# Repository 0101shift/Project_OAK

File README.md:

# ⌚️ Project OAK (Open Art Work)

> *An approach to mimic analogue watch complications in a digital timepiece. One LED at a time.*

> ⚠️ **_Current Version: v0.1_**

> 📝 [_Version History_](Design/LLD_Design/README.md)
---

## 📁 Repository Overview

This repository contains all files related to **Project OAK**, including:

- Design files
- Datasheets
- Pin configuration sheet
- BOM (Bill of Materials)
- Source code and libraries
- Mechanical Integration files

📎 **Project OAK SCH and DSN files can be viewed on [CADLAB.io](https://cadlab.io/project/28412)**

---

## 📖 Project Overview

**Project_OAK** explores a different approach to designing digital timepieces that mimic the beauty and intricacy of **[mechanical watch complications](https://teddybaldassarre.com/blogs/watches/watch-complications?srsltid=AfmBOoqZpyDy6AT5w2ClBAenimUXbEy8DH4jYCP8Jfb1IKT3pajwjdwo)**.

While building a digitalised analogue-style watch is fairly common, recreating some of the mechanical features in a purely digital watch is both challenging and exciting.

> Although current smartwatches offer these functions via complex hardware, my goal is to **implement them using simple hardware** with minimal processing power.

- To add to its uniqueness, the **entire watch will be constructed using stacked PCBs**, which is aimed to be modular and reconfigurable based on our needs.
- The watch is designed with multiple colours and solder finishes, giving it a true electronics-nerd feel.

---

## 🎲 How it Works

> "V0.1 / V0.2" come with a simple design to set and view the time. Here’s an infographic that shows the process

---

## 🔧 Initial Prototype

📌 **[Project_OAK_MAIN_BRD_V0.1 / V0.2](Design/LLD_Design/V0.1/Project_OAK_MAIN_BRD_V0.1_RTC_Change/Project_OAK_MAIN_BRD_V0.1.pdf) is an "engineering sample".**

The primary goal of these variants is to **test all available interfaces, validate battery performance, identify design flaws, and iterate for improvements**.

Consider this board a creative playground, push its limits and explore unique feature additions for the upcoming revision.

---

## 🚀 Down the line

Though the **initial version** of Project_OAK (V0.1 / V0.2) is just a simple watch featuring a **time display** using dual-tone LEDs,

> The Future versions shall include:
> - GMT
> - Minute Repeater (ambitious!)
> - Interactive sensors (Light, IMU, Temp, Step tracking, Buzzer, etc.)
> - Higher-density LED matrix for complex visuals.
> - Position tracking using GPS, LoRa, etc. (ambitious!)
> - Exploring Low-power MCUs for long-life operation.
> - Rechargeable battery option.
> - Solar panel integration for energy harvesting.
> - ...

---

## 💎 Mechanical Integration (v0.1)

> *(These are the outputs from V0.1 variant. Design changes are expected in V0.2)*

---

## ⚙️ Getting Started

### 🔌 Programming the Board

The board can be programmed using the **Arduino IDE** via the ISP function. All the source code can be found in [ProjectOAK/codes](Codes) folder. 

#### 📝 Requirements:
- Arduino UNO/MINI/NANO/MEGA as ISP programmer
- ICSP connection to the Main Board (test points on the bottom side)

#### 💡 ICSP Programming Notes:
- ICSP pins are exposed via **Test Points** arranged in 2.4mm pitch 2x3 connector style
- Either mount **male headers** or directly solder wires for programming
- Board supports **two power options**:
  - `3V Coin Cell (default)`
  - `EXT_3V3_IN` via ICSP (requires mounting resistor R1, which is **DNI by default**)

### ⚡ Arduino IDE Settings

> - Refer to this GitHub repo on how to burn the Bootloader and how to flash code through Arduino IDE [MiniCore](https://github.com/MCUdude/MiniCore)
> - When programming the MAIN_BRD, update the ARDUINO IDE settings as shown below.

#### ❤️‍🔥 Let me know what you think of this project. I'd love to hear your thoughts!

### ✨ Happy Designing!

---

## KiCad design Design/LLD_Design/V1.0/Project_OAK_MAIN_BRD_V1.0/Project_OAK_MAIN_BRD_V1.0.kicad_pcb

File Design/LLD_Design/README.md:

# 📚 Version History

## ⛳️ V1.0 (xxx - WIP)
- Scaling down the overall thickness from 11.4 mm to 8.4 mm (except for the bottom cavity & strap PCB; the thickness of all other PCBs is reduced).
- Planning to change the coin cell from CR2032 to CR2025 and the coin cell holder to BC-2018-TR, reducing the overall battery thickness from 3.2 mm to 2.5 mm.
- Planning to move the push buttons from the top to the bottom side of the main board, since the top cavity PCB height is reduced from 1.6 mm to 1 mm.
- Planning to use a common LED color throughout the design to minimise uneven color diffusion through the PCB dials.
- Planning to increase the pull-up resistor values to reduce leakage.
- Exploring options to include an IMU (LIS2DW12) for future enhancements and upgrading the RTC to RV-3028-C7 for improved performance.
- SW optimisation to reduce current consumption for longer battery life.
- Along with the above changes, all V0.2 updates are also implemented in V1.0.

## 🔮 V0.2 (Engineering Sample2 - merging with V1.0)
- Button circuit connectivity update
- Remove the transistor configuration from the LED matrix directly. Direct connection is simple.
- Battery monitoring circuit implementation (possibly).
- Push button components to be moved towards the inner circle to avoid mechanical collision.
- Top Silk graphics to be removed from the main board.
- Main board & BOT cavity PCB dimension to be increased in the Y-direction, to match the STARP V0 board dimension
- 0E to be replaced with solder-jumpers in the LED matrix section
- DNPed MCU UART resistors
  
## 🔰 V0.1 (Engineering Sample)
- RTC changed from RX8130CE to RV-8263-C7.
- Addressed design issues with rework on the main board. Rework is documented in: [Project_OAK_MAIN_BRD_V0.1_Rework](https://github.com/0101shift/Project_OAK/blob/9e24250cb21920fe7c5c715ad4de5ba70b185401/Reworks/V0.1/README.md). 
- Cell voltage monitoring (along with LED indication) is not implemented in V0.1. Planned for V0.2
- Final testing in progress.

 <div style="background-color:#ffe6e6; padding:10px; border-radius:6px;">
⚠️ <b>Caution:</b> Other layers, except the Main Board, are reused from V0
</div>

## 🚫 V0 (Initial Design - Unreleased)
- Initial board design consists of ATmega328PB MCU, RX8130CE RTC, 36 LEDs (12H + 24M) & 2032 coin cell holder  
- The design was not released for fabrication due to a change in the RTC module.

---

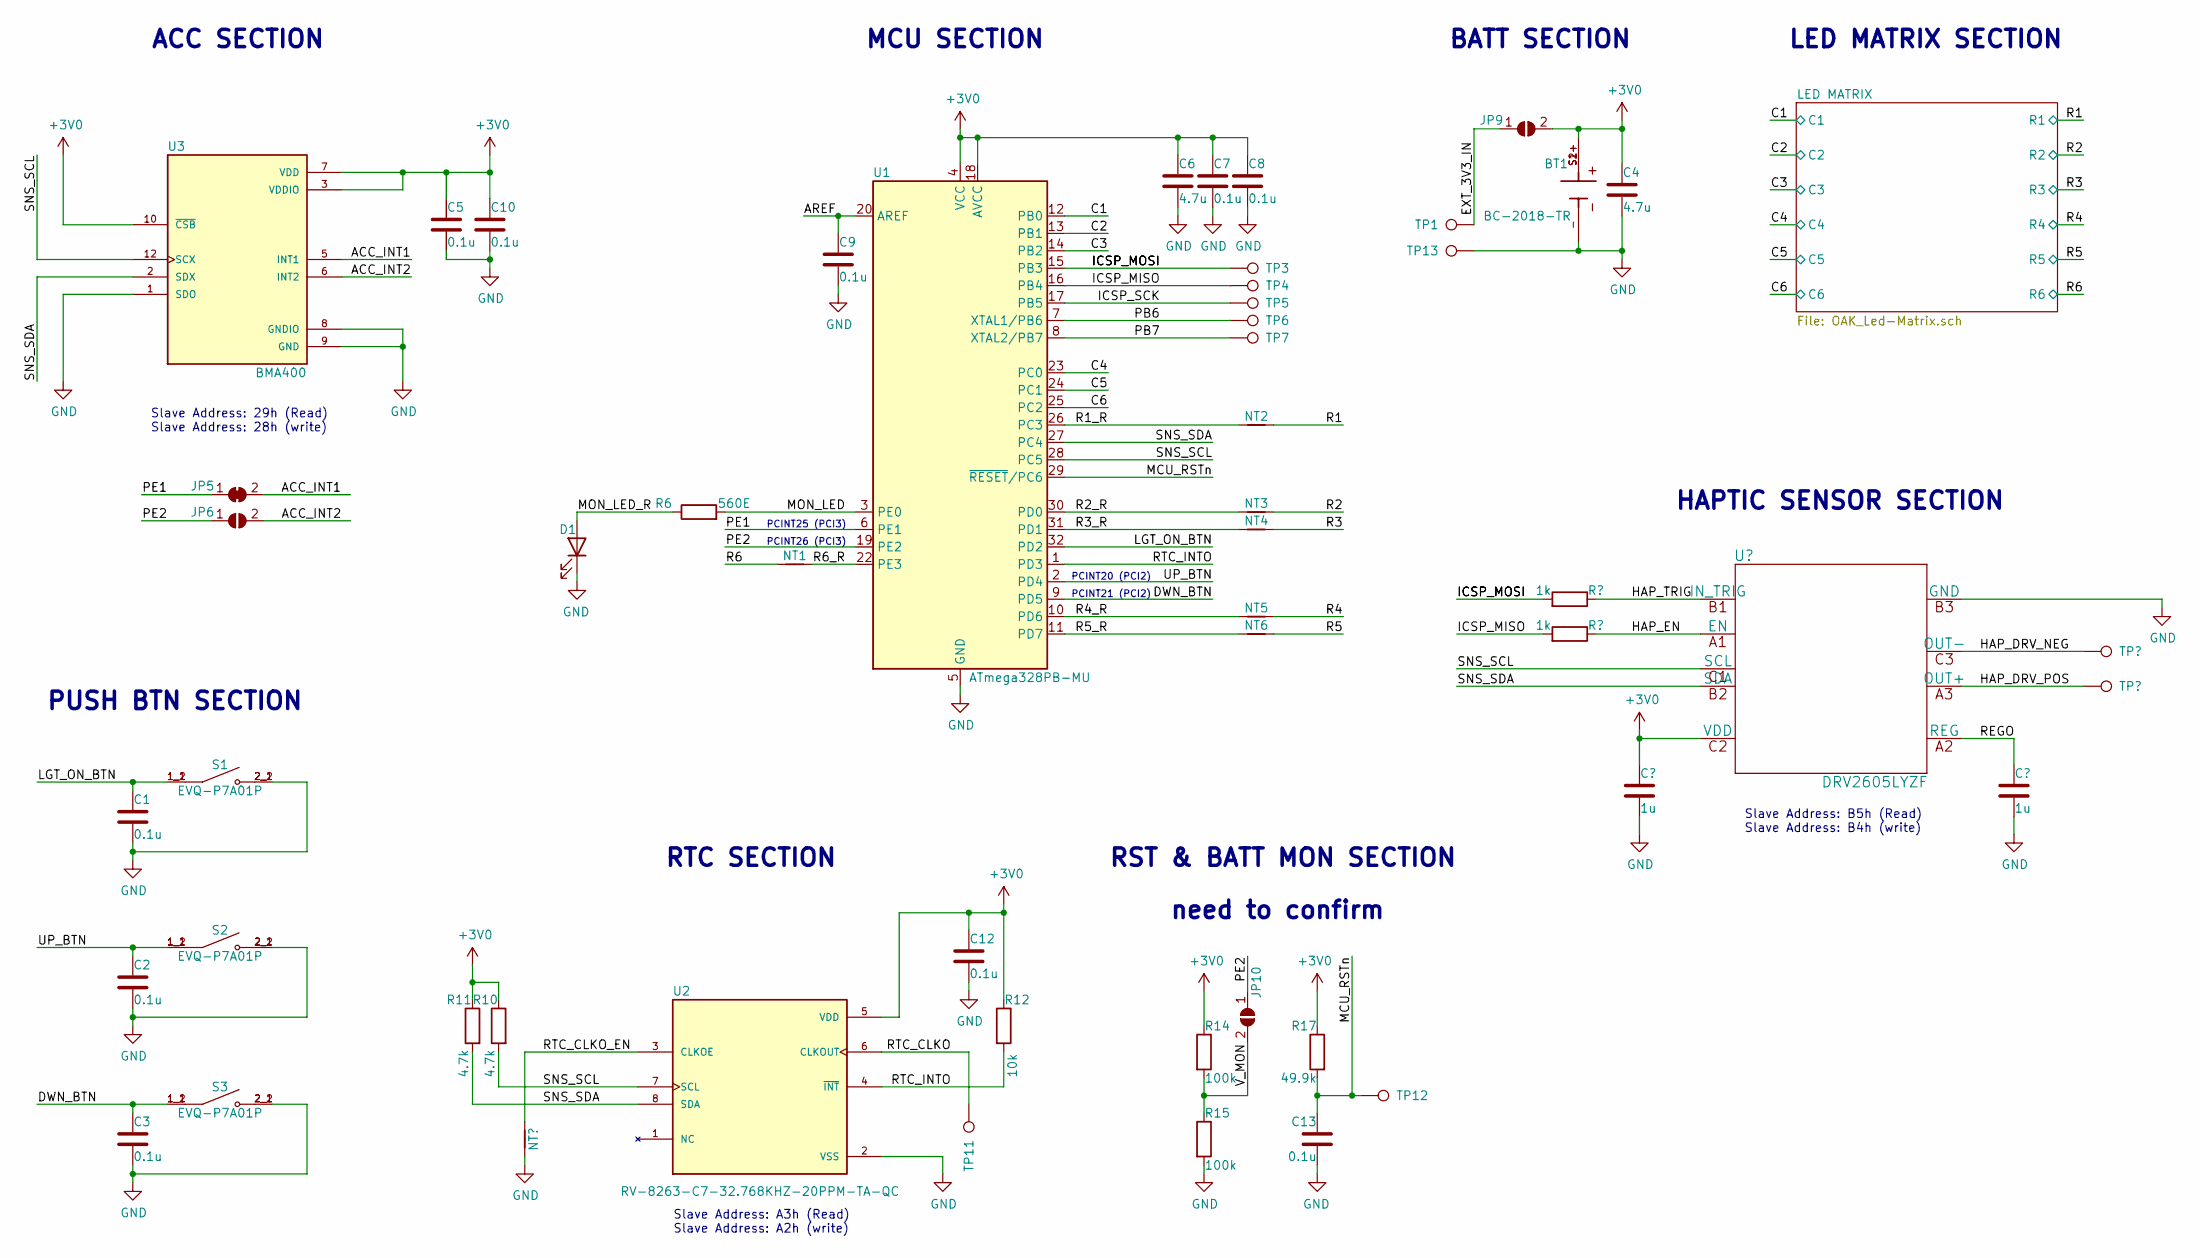
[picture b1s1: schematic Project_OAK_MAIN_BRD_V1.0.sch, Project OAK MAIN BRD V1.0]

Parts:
BT1: BC-2018-TR; BAT_BC-2018-TR; PARTREV B
C1, C2, C3, C5, C7, C8, C9, C10, C12, C13: 0.1u; C_0402_1005Metric
C4, C6: 4.7u; C_0402_1005Metric
D1: LED; LED_0402_1005Metric
JP5: SolderJumper_2_Bridged; SolderJumper-2_Bridged_Pad1.0x1.5mm_custom
JP6, JP9, JP10: SolderJumper_2_Open; SolderJumper-2_Open_Pad1.0x1.5mm_custom
NT1, NT2, NT3, NT4, NT5, NT6: Net-Tie_2; NetTie-2_SMD_Custom
R6: 560E; R_0402_1005Metric
R10, R11: 4.7k; R_0402_1005Metric
R12: 10k; R_0402_1005Metric
R14, R15: 100k; R_0402_1005Metric
R17: 49.9k; R_0402_1005Metric
S1, S2, S3: EVQ-P7A01P; SW_EVQ-P7A01P; Manufacturer_Part_Number EVQ-P7A01P; Mouser Part Number 667-EVQP7A01P
TP1, TP3, TP4, TP5, TP6, TP7, TP11, TP12, TP13: TestPoint; TestPoint_Pad_D1.0mm
U1: ATmega328PB-MU; QFN-32-1EP_5x5mm_P0.5mm_EP3.1x3.1mm
U2: RV-8263-C7-32.768KHZ-20PPM-TA-QC; PARTREV 1.0
U3: BMA400; XDCR_BMA400

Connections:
+3V0: BT1.S1+, BT1.S2+, C4.1, C5.1, C6.1, C7.1, C8.1, C10.1, C12.1, JP9.2 (B), R10.1, R11.1, R12.1, R14.1, R17.1, U1.4 (VCC), U1.18 (AVCC), U2.5 (VDD), U3.3 (VDDIO), U3.7 (VDD), U3.10 (~CSB); also elsewhere on the board
/ACC_INT1: JP5.2 (B), U3.5 (INT1)
/ACC_INT2: JP6.2 (B), U3.6 (INT2)
/AREF: C9.1, U1.20 (AREF)
/C1: U1.12 (PB0); also elsewhere on the board
/C2: U1.13 (PB1); also elsewhere on the board
/C3: U1.14 (PB2); also elsewhere on the board
/C4: U1.23 (PC0); also elsewhere on the board
/C5: U1.24 (PC1); also elsewhere on the board
/C6: U1.25 (PC2); also elsewhere on the board
/DWN_BTN: C3.1, S3.1_1, S3.1_2, U1.9 (PD5)
/EXT_3V3_IN: JP9.1 (A), TP1.1
/ICSP_MISO: TP4.1, U1.16 (PB4); also elsewhere on the board
/ICSP_MOSI: TP3.1, U1.15 (PB3); also elsewhere on the board
/ICSP_SCK: TP5.1, U1.17 (PB5)
/LGT_ON_BTN: C1.1, S1.1_1, S1.1_2, U1.32 (PD2)
/MCU_RSTn: C13.1, R17.2, TP12.1, U1.29 (~RESET~/PC6)
/MON_LED: R6.2, U1.3 (PE0)
/MON_LED_R: D1.2 (A), R6.1
/PB6: TP6.1, U1.7 (XTAL1/PB6)
/PB7: TP7.1, U1.8 (XTAL2/PB7)
/PE1: JP5.1 (A), U1.6 (PE1)
/PE2: JP6.1 (A), JP10.1 (A), U1.19 (PE2)
/R1: NT2.2; also elsewhere on the board
/R1_R: NT2.1, U1.26 (PC3)
/R2: NT3.2; also elsewhere on the board
/R2_R: NT3.1, U1.30 (PD0)
/R3: NT4.2; also elsewhere on the board
/R3_R: NT4.1, U1.31 (PD1)
/R4: NT5.2; also elsewhere on the board
/R4_R: NT5.1, U1.10 (PD6)
/R5: NT6.2; also elsewhere on the board
/R5_R: NT6.1, U1.11 (PD7)
/R6: NT1.1; also elsewhere on the board
/R6_R: NT1.2, U1.22 (PE3)
/RTC_CLKO: TP11.1, U2.6 (CLKOUT)
/RTC_CLKO_EN: U2.3 (CLKOE); also elsewhere on the board
/RTC_INTO: R12.2, U1.1 (PD3), U2.4 (~INT)
/SNS_SCL: R10.2, U1.28 (PC5), U2.7 (SCL), U3.12 (SCX); also elsewhere on the board
/SNS_SDA: R11.2, U1.27 (PC4), U2.8 (SDA), U3.2 (SDX); also elsewhere on the board
/UP_BTN: C2.1, S2.1_1, S2.1_2, U1.2 (PD4)
/V_MON: JP10.2 (B), R14.2, R15.1
GND: BT1.-, C1.2, C2.2, C3.2, C4.2, C5.2, C6.2, C7.2, C8.2, C9.2, C10.2, C12.2, C13.2, D1.1 (K), R15.2, S1.2_1, S1.2_2, S2.2_1, S2.2_2, S3.2_1, S3.2_2, TP13.1, U1.5 (GND), U1.21 (GND), U1.33 (GND), U2.2 (VSS), U3.1 (SDO), U3.8 (GNDIO), U3.9 (GND); also elsewhere on the board

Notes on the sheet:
PUSH BTN SECTION
BATT SECTION
MCU SECTION
Slave Address: A3h (Read) Slave Address: A2h (write)
LED MATRIX SECTION
ACC SECTION
need to confirm
RST & BATT MON SECTION
Slave Address: 29h (Read) Slave Address: 28h (write)
RTC SECTION
PCINT25 (PCI3)
PCINT26 (PCI3)
PCINT20 (PCI2)
PCINT21 (PCI2)
HAPTIC SENSOR SECTION
Slave Address: B5h (Read) Slave Address: B4h (write)

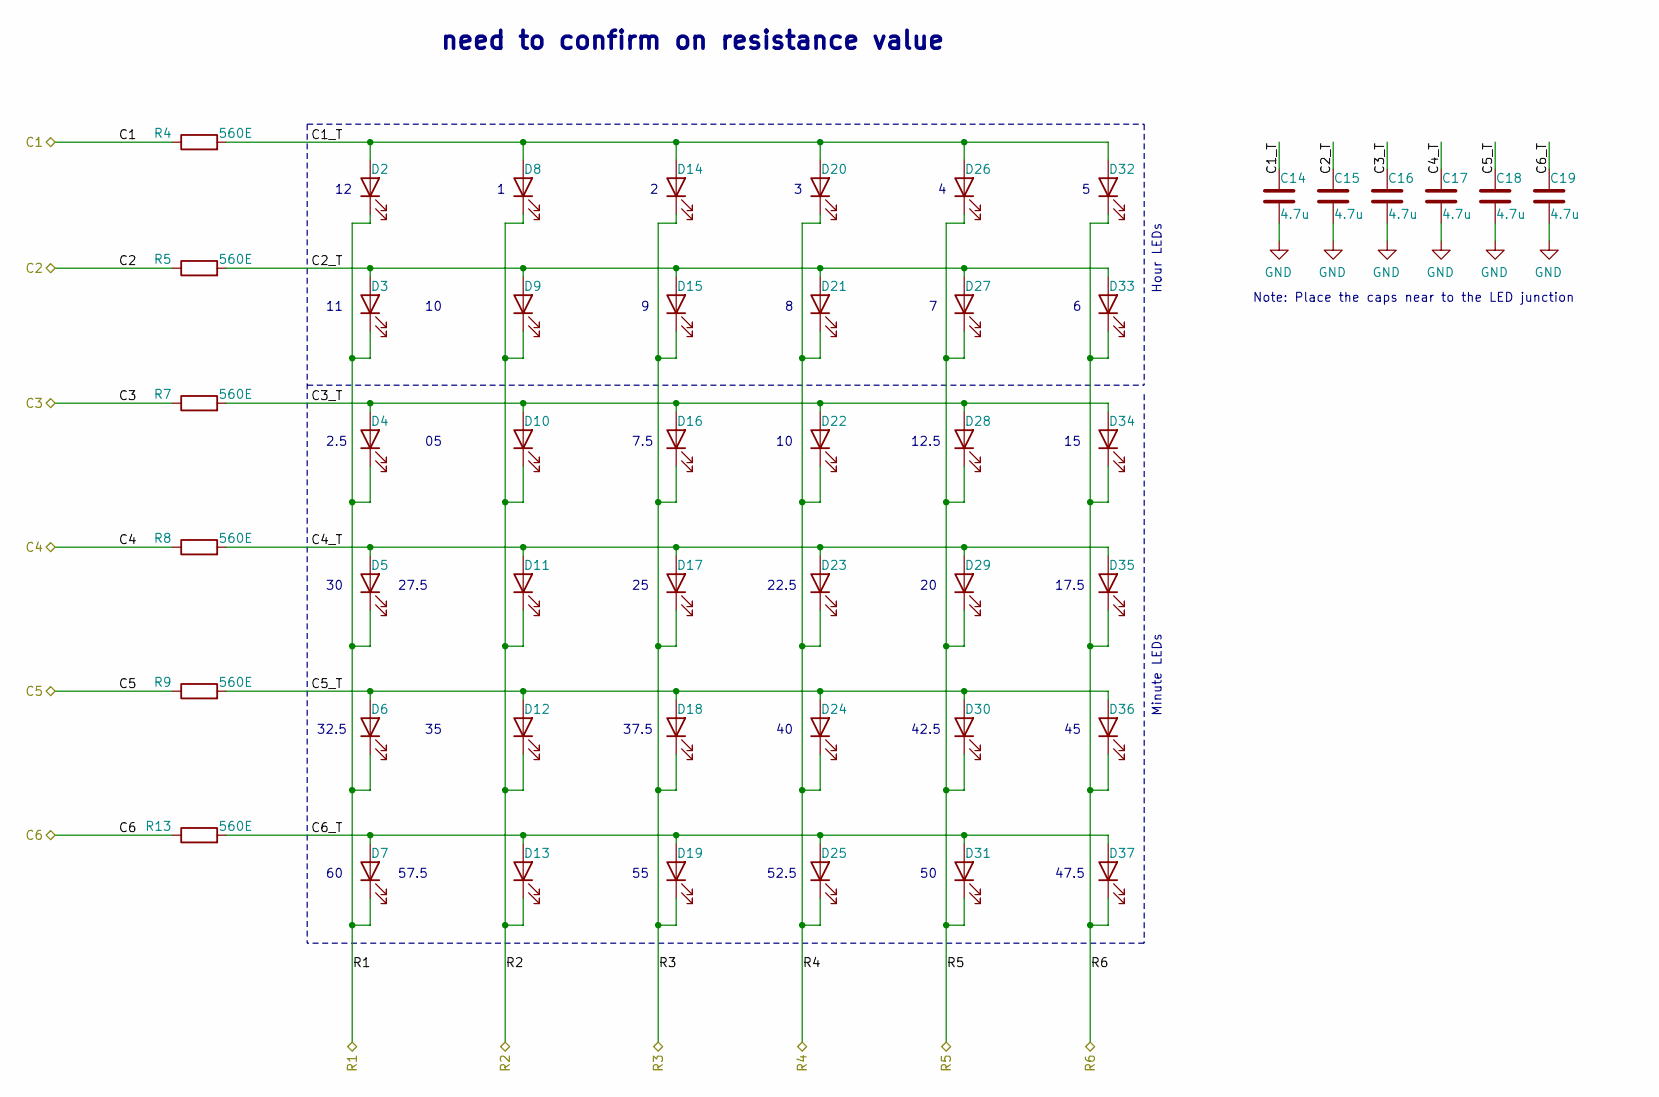
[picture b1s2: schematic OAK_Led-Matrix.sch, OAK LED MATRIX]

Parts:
C14, C15, C16, C17, C18, C19: 4.7u; C_0402_1005Metric
D2, D3, D4, D5, D6, D7, D8, D9, D10, D11, D12, D13, D14, D15, D16, D17, D18, D19, D20, D21, D22, D23, D24, D25, D26, D27, D28, D29, D30, D31, D32, D33, D34, D35, D36, D37: LED; LED_0402_1005Metric
R4, R5, R7, R8, R9, R13: 560E; R_0402_1005Metric

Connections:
/C1: R4.1; also elsewhere on the board
/C2: R5.1; also elsewhere on the board
/C3: R7.1; also elsewhere on the board
/C4: R8.1; also elsewhere on the board
/C5: R9.1; also elsewhere on the board
/C6: R13.1; also elsewhere on the board
/LED MATRIX/C1_T: C14.1, D2.2 (A), D8.2 (A), D14.2 (A), D20.2 (A), D26.2 (A), D32.2 (A), R4.2
/LED MATRIX/C2_T: C15.1, D3.2 (A), D9.2 (A), D15.2 (A), D21.2 (A), D27.2 (A), D33.2 (A), R5.2
/LED MATRIX/C3_T: C16.1, D4.2 (A), D10.2 (A), D16.2 (A), D22.2 (A), D28.2 (A), D34.2 (A), R7.2
/LED MATRIX/C4_T: C17.1, D5.2 (A), D11.2 (A), D17.2 (A), D23.2 (A), D29.2 (A), D35.2 (A), R8.2
/LED MATRIX/C5_T: C18.1, D6.2 (A), D12.2 (A), D18.2 (A), D24.2 (A), D30.2 (A), D36.2 (A), R9.2
/LED MATRIX/C6_T: C19.1, D7.2 (A), D13.2 (A), D19.2 (A), D25.2 (A), D31.2 (A), D37.2 (A), R13.2
/R1: D2.1 (K), D3.1 (K), D4.1 (K), D5.1 (K), D6.1 (K), D7.1 (K); also elsewhere on the board
/R2: D8.1 (K), D9.1 (K), D10.1 (K), D11.1 (K), D12.1 (K), D13.1 (K); also elsewhere on the board
/R3: D14.1 (K), D15.1 (K), D16.1 (K), D17.1 (K), D18.1 (K), D19.1 (K); also elsewhere on the board
/R4: D20.1 (K), D21.1 (K), D22.1 (K), D23.1 (K), D24.1 (K), D25.1 (K); also elsewhere on the board
/R5: D26.1 (K), D27.1 (K), D28.1 (K), D29.1 (K), D30.1 (K), D31.1 (K); also elsewhere on the board
/R6: D32.1 (K), D33.1 (K), D34.1 (K), D35.1 (K), D36.1 (K), D37.1 (K); also elsewhere on the board
GND: C14.2, C15.2, C16.2, C17.2, C18.2, C19.2; also elsewhere on the board

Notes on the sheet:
Hour LEDs
Minute LEDs
2.5
7.5
12.5
17.5
22.5
27.5
32.5
37.5
42.5
47.5
52.5
57.5
need to confirm on resistance value
Note: Place the caps near to the LED junction

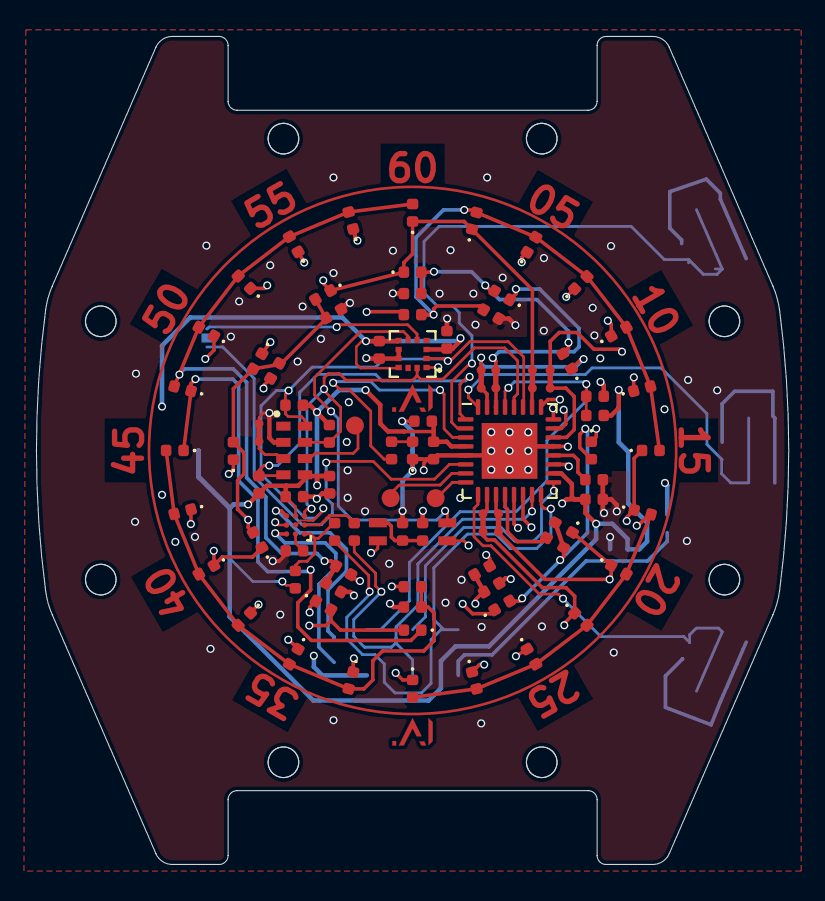
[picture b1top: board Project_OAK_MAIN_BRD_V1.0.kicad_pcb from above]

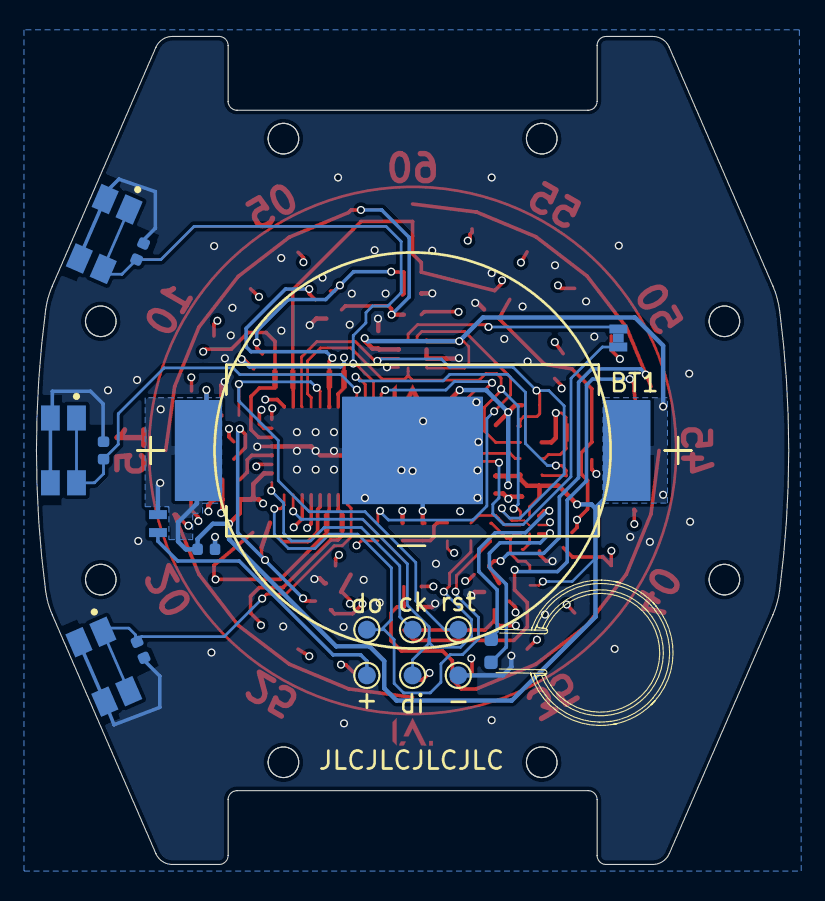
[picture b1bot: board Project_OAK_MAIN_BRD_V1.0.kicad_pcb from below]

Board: 4 copper layers, 41.8 x 46.0 mm, 104 parts (19 on the bottom side), 54 nets.

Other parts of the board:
BT1#2: BC-2018-TR; BAT_BC-2018-TR
C11, C20: 1u; C_0402_1005Metric
NT7: Net-Tie_2; NetTie-2_SMD_Custom
R1, R2: 1k; R_0402_1005Metric
R3: 100k; R_0402_1005Metric
TP2, TP8: TestPoint; TestPoint_Pad_D1.0mm
U4: DRV2605LYZF; DRV2605LYZFR

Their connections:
+3V0: BT1#2.S1+, BT1#2.S2+, C11.1, R3.1, U4.C2; also elsewhere on the board
/HAP_DRV_NEG: TP2.1, U4.C3
/HAP_DRV_POS: TP8.1, U4.A3
/HAP_EN: R2.1, R3.2, U4.A1
/HAP_TRIG: R1.1, U4.B1
/ICSP_MISO: R2.2; also elsewhere on the board
/ICSP_MOSI: R1.2; also elsewhere on the board
/REGO: C20.1, U4.A2
/RTC_CLKO_EN: NT7.1; also elsewhere on the board
/SNS_SCL: U4.C1; also elsewhere on the board
/SNS_SDA: U4.B2; also elsewhere on the board
GND: BT1#2.-, C11.2, C20.2, NT7.2, U4.B3; also elsewhere on the board

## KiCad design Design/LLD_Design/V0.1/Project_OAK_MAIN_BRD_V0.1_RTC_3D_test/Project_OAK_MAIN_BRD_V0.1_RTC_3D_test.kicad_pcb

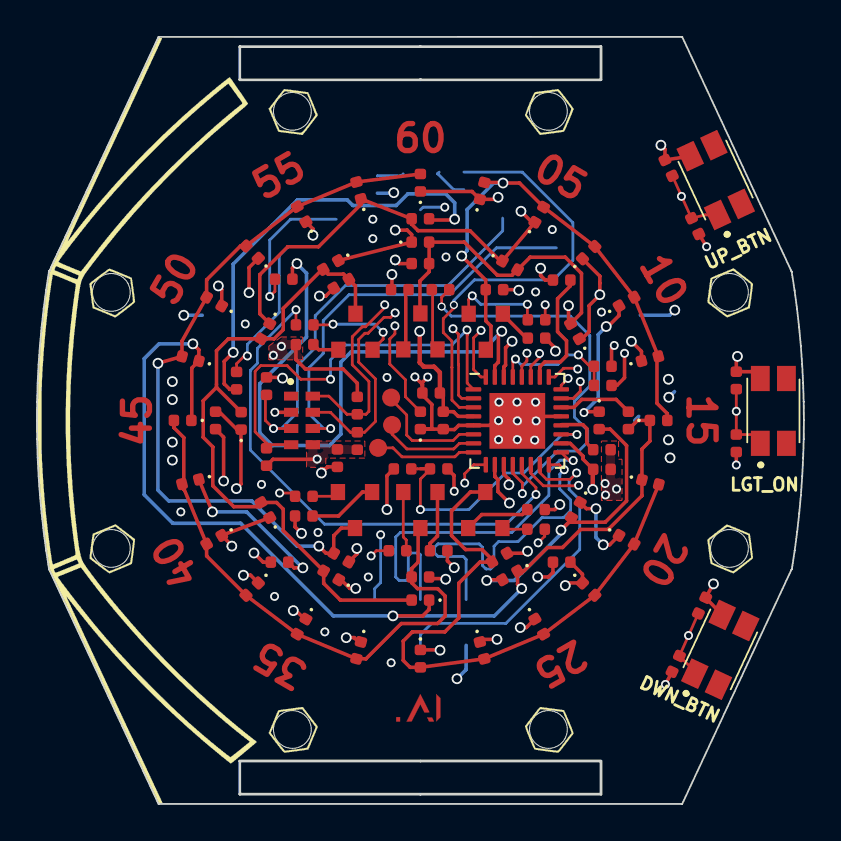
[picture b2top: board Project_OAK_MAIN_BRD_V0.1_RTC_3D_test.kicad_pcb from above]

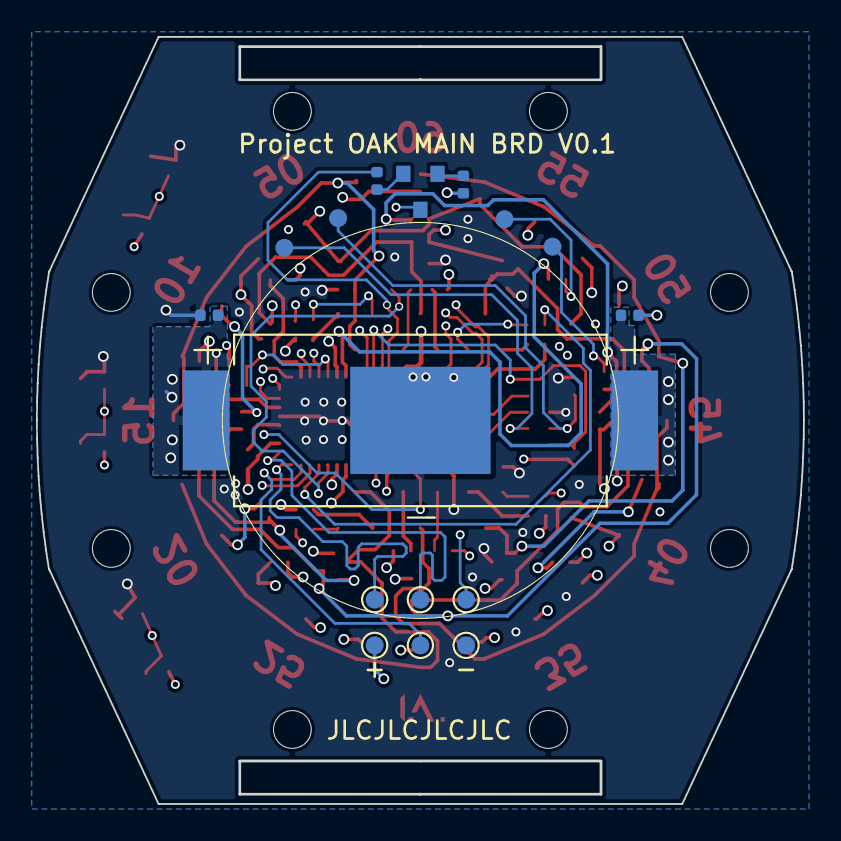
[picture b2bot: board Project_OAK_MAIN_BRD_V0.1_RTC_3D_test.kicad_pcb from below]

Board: 6 copper layers, 42.6 x 42.6 mm, 112 parts (16 on the bottom side), 62 nets.

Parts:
BT1: BC-2003; BAT_BC-2003
C1, C2, C3, C7, C8, C9, C12, C13: 0.1u; C_0402_1005Metric
C4, C6, C14, C15, C16, C17, C18, C19: 4.7u; C_0402_1005Metric
D1, D2, D3, D4, D5, D6, D7, D8, D9, D10, D11, D12, D13, D14, D15, D16, D17, D18, D19, D20, D21, D22, D23, D24, D25, D26, D27, D28, D29, D30, D31, D32, D33, D34, D35, D36, D37: LED; LED_0402_1005Metric
Q1, Q2, Q3, Q4, Q5, Q6, Q7: BC547; SOT-23
R1, R28, R29, R30, R31, R32, R33: 0E; R_0402_1005Metric
R2, R3, R4, R7, R14, R15, R17: 10k; R_0402_1005Metric
R5: 1K; R_0402_1005Metric
R6, R13, R18, R19, R22, R23, R26: 10K; R_0402_1005Metric
R8, R9: 1k; R_0402_1005Metric
R10, R11, R12: 4.7K; R_0402_1005Metric
R16, R20, R21, R24, R25, R27: 120E; R_0402_1005Metric
S1, S2, S3: EVQ-P7A01P; EVQP7J01P
TP1, TP2, TP3, TP4, TP5, TP6, TP7, TP8, TP9, TP10, TP11, TP12, TP13: TestPoint; TestPoint_Pad_D1.0mm
U1: ATmega328PB-MU; QFN-32-1EP_5x5mm_P0.5mm_EP3.1x3.1mm
U2: RV-8263-C7-32.768KHZ-20PPM-TA-QC

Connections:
+3V0: BT1.S1+, BT1.S2+, C4.1, C6.1, C7.1, C8.1, C12.1, R1.2, R2.1, R3.1, R4.1, R5.2, R10.1, R11.1, R12.1, R14.1, R16.2, R17.1, R20.2, R21.2, R24.2, R25.2, R27.2, U1.4, U1.18, U2.5
/+3V0_MON_LED: R6.2, U1.3
/+3V0_VOL_MON: R14.2, R15.1, U1.19
/AREF: C9.1, U1.20
/C1: R26.1, U1.12
/C1_T: C14.1, D2.2, D8.2, D14.2, D20.2, D26.2, D32.2, Q7.3
/C2: R23.1, U1.13
/C2_T: C15.1, D3.2, D9.2, D15.2, D21.2, D27.2, D33.2, Q6.3
/C3: R22.1, U1.14
/C3_T: C16.1, D4.2, D10.2, D16.2, D22.2, D28.2, D34.2, Q5.3
/C4: R19.1, U1.23
/C4_T: C17.1, D5.2, D11.2, D17.2, D23.2, D29.2, D35.2, Q4.3
/C5: R18.1, U1.24
/C5_T: C18.1, D6.2, D12.2, D18.2, D24.2, D30.2, D36.2, Q3.3
/C6: R13.1, U1.25
/C6_T: C19.1, D7.2, D13.2, D19.2, D25.2, D31.2, D37.2, Q2.3
/DBG_RX: R8.2, TP9.1
/DBG_TX: R9.2, TP10.1
/DWN_BTN: C3.1, R4.2, S3.1, U1.9
/EXT_3V3_IN: R1.1, TP1.1
/ICSP_MISO: TP4.1, U1.16
/ICSP_MOSI: TP3.1, U1.15
/ICSP_SCK: TP5.1, U1.17
/LGT_ON_BTN: C1.1, R2.2, S1.1, U1.32
/MCU_RSTn: C13.1, R17.2, TP12.1, U1.29
/PB6: TP6.1, U1.7
/PB7: TP7.1, U1.8
/PE1: TP2.1, U1.6
/R1: D2.1, D3.1, D4.1, D5.1, D6.1, D7.1, R29.2
/R1_R: R29.1, U1.26
/R2: D8.1, D9.1, D10.1, D11.1, D12.1, D13.1, R32.2
/R2_R: R8.1, R32.1, U1.30
/R3: D14.1, D15.1, D16.1, D17.1, D18.1, D19.1, R33.2
/R3_R: R9.1, R33.1, U1.31
/R4: D20.1, D21.1, D22.1, D23.1, D24.1, D25.1, R30.2
/R4_R: R30.1, U1.10
/R5: D26.1, D27.1, D28.1, D29.1, D30.1, D31.1, R31.2
/R5_R: R31.1, U1.11
/R6: D32.1, D33.1, D34.1, D35.1, D36.1, D37.1, R28.1
/R6_R: R28.2, U1.22
/RTC_CLKO: TP11.1, U2.6
/RTC_CLKO_EN: R7.1, TP8.1, U2.3
/RTC_INTO: R12.2, U1.1, U2.4
/RTC_SCL: R10.2, U1.28, U2.7
/RTC_SDA: R11.2, U1.27, U2.8
/UP_BTN: C2.1, R3.2, S2.1, U1.2
GND: BT1.-, C1.2, C2.2, C3.2, C4.2, C6.2, C7.2, C8.2, C9.2, C12.2, C13.2, C14.2, C15.2, C16.2, C17.2, C18.2, C19.2, D1.1, R7.2, R15.2, S1.2, S2.2, S3.2, TP13.1, U1.5, U1.21, U1.33, U2.2
unnamed: D1.2, Q1.3
unnamed: Q1.1, R5.1
unnamed: Q1.2, R6.1
unnamed: Q2.1, R16.1
unnamed: Q2.2, R13.2
unnamed: Q3.1, R20.1
unnamed: Q3.2, R18.2
unnamed: Q4.1, R21.1
unnamed: Q4.2, R19.2
unnamed: Q5.1, R24.1
unnamed: Q5.2, R22.2
unnamed: Q6.1, R25.1
unnamed: Q6.2, R23.2
unnamed: Q7.1, R27.1
unnamed: Q7.2, R26.2

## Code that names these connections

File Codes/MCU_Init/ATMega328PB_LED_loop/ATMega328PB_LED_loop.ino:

/*********************************************************************
  Simple AVR sketch to blink Hour & Minute LEDs in a random loop
  For WATCH LEDs mapping, check the Project_OAK_MCU_Pinouts.xlsx excel
**********************************************************************/

#include <avr/io.h>
#include <util/delay.h>

typedef struct {
  volatile uint8_t *port;
  uint8_t pin;
} led;

led leds[] = {
  {&PORTB, PB0}, {&PORTB, PB1}, {&PORTB, PB2},
  {&PORTC, PC0}, {&PORTC, PC1}, {&PORTC, PC2},
  {&PORTC, PC3}, {&PORTD, PD0}, {&PORTD, PD1},
  {&PORTD, PD6}, {&PORTD, PD7}, {&PORTE, PE3}
};

uint8_t ledcount = sizeof(leds) / sizeof(leds[0]);

void setup()
{
  for (uint8_t i = 0; i < ledcount; i++)
  {
    if (leds[i].port == &PORTB)
    {
      DDRB |= (1 << leds[i].pin);
    }
    else if (leds[i].port == &PORTC)
    {
      DDRC |= (1 << leds[i].pin);
    }
    else if (leds[i].port == &PORTD)
    {
      DDRD |= (1 << leds[i].pin);
    }
    else if (leds[i].port == &PORTE)
    {
      DDRE |= (1 << leds[i].pin);
    }
  }
}

int main (void)
{
  setup();

  while (1) {
    ledblink(100);
  }
  return 0;
}

void ledblink (uint16_t delaytime)
{
  for (uint8_t i = 0; i < ledcount / 2; i++)
  {
    *(leds[i].port) ^= (1 << leds[i].pin);
    _delay_ms(delaytime);
    for (uint8_t j = ledcount / 2; j < ledcount; j++)
    {
      *(leds[j].port) ^= (1 << leds[j].pin);
      _delay_ms(delaytime);
    }
  }
}

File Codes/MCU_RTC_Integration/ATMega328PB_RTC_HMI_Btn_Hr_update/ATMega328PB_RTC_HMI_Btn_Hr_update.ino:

/**********************************************************************************************************
  Simple AVR sketch demonstrate the interface of RTC sensor RV-8263-C7 with ATMega328PB. This code is to
  execute Hour, Minute & MI functions of the RTC sensor and outputs the data using on-board LEDs (visulization).
  Post power on, MCU goes to sleep and wakes up on interrupt generated either by the RTC sensor (every minute)
  or with button press (PWR BTN). based on the button press duration, specific set of actions are performed.
  If button press short (50ms), the device outputs RTC sensor data by lighting up the LEDs (Time Indication)
  and goes back to sleep. If button press long (1000ms), the device wakes up from pwr-down mode and stays
  in active state by blinking all the LEDs onboard (100ms). This allows user to update Time by pressing
  UP & DWN button to adjust Hour time respectively. Once updated time, the device is put back to sleep 
  by short pressing the PWR button.

  Sketch uses "OakLedMatrix" lib which takes care of mapping LED pins to their respective Hr/Min positions
  Sketch uses "RV-8263-C7" lib which takes care of interface between MCU and RV-8263-C7 RTC sensor

  Here are the list of registers that are modified / accessed in this program

  |Register|         |Function|      |Bit7|  |Bit6|  |Bit5|  |Bit4|  |Bit3|  |Bit2|  |Bit1|  |Bit0|
  |                                                                                               |
  |  01h   |         |Control2|      |AIE |  | AF |  | MI |  |HMI |  | TF |  | FD|   | FD |  | FD |
  |  04h   |         |Seconds|       | OS |  | 40 |  | 20 |  | 10 |  | 8  |  | 4 |   | 2 |   | 1  |
  |  05h   |         |minutes|       | X  |  | 40 |  | 20 |  | 10 |  | 8  |  | 4 |   | 2 |   | 1  |
  |  06h   |          |Hours|        | X  |  | X  |  |AMPM|  | 10 |  | 8  |  | 4 |   | 2 |   | 1  |
  |  07h   |          |Date|         | X  |  | X  |  | 20 |  | 10 |  | 8  |  | 4 |   | 2 |   | 1  |
  |  08h   |         |Weekday|       | X  |  | X  |  | X  |  | X  |  | X  |  | 4 |   | 2 |   | 1  |
  |  09h   |          |Month|        | X  |  | X  |  | X  |  | 10 |  | 8  |  | 4 |   | 2 |   | 1  |
  |  0Ah   |          |Year|         | 80 |  | 40 |  | 20 |  | 10 |  | 8  |  | 4 |   | 2 |   | 1  |
  |  11h   |       |Timer Mode|      | X  |  | X  |  | X  |  | TD |  | TD |  |TE |   |TIE|  |TI_TP|
**********************************************************************************************************/

#include <avr/io.h>
#include <avr/sleep.h>
#include <util/delay.h>
#include <RV-8263-C7.h>
#include <OakLedMatrix.h>
#include <math.h>

#define HMI_INTERRUPT_PIN PD3   // RTC interrupt (INT1)
#define PWR_BUTTON_PIN PD2   // Push button interrupt (INT0)
#define UP_BUTTON_PIN PD4       // Button to increase value
#define DWN_BUTTON_PIN PD5      // Button to decrease value
#define SHORT_PRESS_DURATION 50   // Duration in milliseconds
#define LONG_PRESS_DURATION 1000  // Duration in milliseconds

volatile bool wakeUpFlag = false;      // Interrupt flag to indicate wake-up event
volatile uint16_t pressDuration = 0;   // Stores button press timestamp
volatile bool buttonPressed = false;   // Flag for button press event
volatile uint8_t stayAwake = false;    // Flag to keep MCU awake
volatile bool inUpdateMode = false; // Flag to track update mode

void setup() {
  initMatrix();
  initRTC();
  _delay_ms(1000);

  // Configure RTC for Half-Minute Interrupt (HMI)
  writeRegister(0x01, 0b00100000); // Set periodic interrupt to Minute
  writeRegister(0x11, 0b00011001); // Enable periodic interrupt

  // Configure PD3 (INT1) for RTC interrupt (falling edge)
  DDRD &= ~(1 << HMI_INTERRUPT_PIN); // Set PD3 as input
  PORTD |= (1 << HMI_INTERRUPT_PIN); // Enable pull-up resistor on PD3
  EICRA |= (1 << ISC11); // Falling edge triggers INT1
  EICRA &= ~(1 << ISC10);
  EIMSK |= (1 << INT1);  // Enable INT1 interrupt

  // Configure PD2 (INT0) for push-button wake-up (falling edge)
  DDRD &= ~(1 << PWR_BUTTON_PIN); // Set PD2 as input
  PORTD |= (1 << PWR_BUTTON_PIN); // Enable pull-up resistor on PD3
  EICRA |= (1 << ISC01);
  EICRA &= ~(1 << ISC00);
  EIMSK |= (1 << INT0);  // Enable INT0 interrupt

  // Configure navigation buttons (PD4, PD5) as inputs with pull-ups
  DDRD &= ~((1 << UP_BUTTON_PIN) | (1 << DWN_BUTTON_PIN));
  PORTD |= (1 << UP_BUTTON_PIN) | (1 << DWN_BUTTON_PIN);

  sei(); // Enable global interrupts
}

// Interrupt Service Routine (ISR) for RTC wake-up on PD3 (INT1)
ISR(INT1_vect) {
  wakeUpFlag = true;
}

// Interrupt Service Routine (ISR) for push-button wake-up on PD2 (INT0)
ISR(INT0_vect) {
  buttonPressed = true;  // Flag to handle the button press in the main loop
}

void loop() {
  if (buttonPressed) {
    _delay_ms(50);  // Basic debounce delay
    buttonPressed = false;

    // Measure press duration
    pressDuration = 0;
    while (!(PIND & (1 << PWR_BUTTON_PIN))) {
      _delay_ms(10);  // Increment duration in 10ms steps
      pressDuration += 10;
      if (pressDuration >= LONG_PRESS_DURATION) {
        break;  // Stop counting if long press is detected
      }
    }

    if (pressDuration >= LONG_PRESS_DURATION) {
      stayAwake = true;  // Set stayAwake, preventing sleep
      functionLongPress();
      enterUpdateMode();
    } else if (pressDuration >= SHORT_PRESS_DURATION) {
      stayAwake = false;  // Allow sleep
      functionShortPress();
    }
  }

  if (wakeUpFlag) {
    wakeUpFlag = false;
    displayTime();
  }

  if (!stayAwake && !inUpdateMode) {
    enterSleepMode();
  }
}

// Function to enter power-down sleep mode
void enterSleepMode() {
  set_sleep_mode(SLEEP_MODE_PWR_DOWN); // Power-down mode
  sleep_enable(); // Enable sleep mode
  sleep_cpu(); // Enter sleep mode (wait for interrupt)
  sleep_disable(); // Disable sleep after waking up
}

// Function to get RTC time and display it using LED matrix
void displayTime() {
  uint8_t hours, minutes, seconds, date, day, month, year;
  const char period[3];

  getTime(hours, minutes, seconds, date, day, month, year, period);

  // Convert minutes to corresponding LED index (2.5 min per LED)
  uint8_t minuteMap = round(minutes / 2.5);

  // Show hour and minute time for 1 second
  uint16_t displayDuration = 500 / 10;  // 100ms per toggle for 0.5 second

  for (uint16_t i = 0; i < displayDuration; i++) {
    LedClockHourTime(hours);
    _delay_ms(5);
    LedClockMinuteTime(minuteMap);
    _delay_ms(5);
  }

  deactivateLedMatrix(); // Turn off LEDs
}

// === Short Press Function ===
void functionShortPress() {
  displayTime();
}

// === Long Press Function ===
void functionLongPress() {
  activateLedMatrixAll();
  _delay_ms(100);
  deactivateLedMatrix();
  _delay_ms(100);
}

// === LED Navigation Mode for Setting Hour ===
void enterUpdateMode() {
  inUpdateMode = true;
  uint8_t newHour = 12; // Default hour selection
  uint8_t up_button_state, dwn_button_state, pwr_button_state;
  uint8_t last_button_state = 0;

  while (inUpdateMode) {
    // Read button states
    up_button_state = PIND & (1 << UP_BUTTON_PIN);
    dwn_button_state = PIND & (1 << DWN_BUTTON_PIN);
    pwr_button_state = PIND & (1 << PWR_BUTTON_PIN);

    // If any button was pressed
    if ((up_button_state == 0 && last_button_state != 0) ||
        (dwn_button_state == 0 && last_button_state != 0) ||
        (pwr_button_state == 0 && last_button_state != 0)) {

      _delay_ms(50); // Debounce delay

      // Increase hour
      if ((PIND & (1 << UP_BUTTON_PIN)) == 0) {
        newHour = (newHour == 12) ? 1 : newHour + 1;
      }

      // Decrease hour
      if ((PIND & (1 << DWN_BUTTON_PIN)) == 0) {
        newHour = (newHour == 1) ? 12 : newHour - 1;
      }

      // Confirm and update RTC
      if ((PIND & (1 << PWR_BUTTON_PIN)) == 0) {
        updateRTC(newHour);
        inUpdateMode = false;
        return;
      }
    }

    // Display hour LED navigation
    LedClockHourTime(newHour);
    _delay_ms(100); // Small delay to improve responsiveness

    // Store last button state
    last_button_state = up_button_state | dwn_button_state | pwr_button_state;
  }
}

// === Update RTC with New Hour ===
void updateRTC(uint8_t newHour) {
  uint8_t nowHour, nowMinutes, nowSeconds, nowDate, nowDay, nowMonth, nowYear;
  const char nowPeriod[3];

  getTime(nowHour, nowMinutes, nowSeconds, nowDate, nowDay, nowMonth, nowYear, nowPeriod);
  updateTime(newHour, nowMinutes, nowSeconds, nowDate, nowDay, nowMonth, nowYear, nowPeriod);
}

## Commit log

2024-09-01 Initial Commit
    These are the basic codes that is used to perform basic bring-up on Project_OAK_MAIN_BRD_V0.1 board.
2024-09-01 Project Initial Commit
2024-09-01 Backlink to CADLAB.io has been added.
2024-09-04 Added RTC sensor Initialization codes
2024-09-05 Added multiple INT wake function for MCU with RTC timestamp
2024-09-11 Updated README.md with Steps to program the Main Board
2024-09-11 Added datasheet and gitignore list
2024-09-11 removed PPTX file
2024-09-11 Rename list.gitignore to .gitignore
2024-09-15 Updated Blink code, SCH comments & added LED mapping details
2024-09-16 Added LED loop code
2024-11-25 removed LED_loop & added OakLedMartix test codes
2025-01-28 Added RTC library and RTC function initialization codes
2025-01-28 updated OakLedMatrix library
2025-02-04 added ATMega & RTC integration code
2025-02-10 added random led animation to the library
2025-07-06 rearranged design files based on versions and added mechanical DXF files
2025-08-02 removed 3D test folder
2025-08-03 added Project OAK V1.0 build SW
2025-08-04 Added product mockup images
2025-08-04 Added reference doc folder
2025-08-04 updated Project OAK Exploded Image
2025-08-04 Updated links in README.md
2025-08-05 updated MCU & RTC links
2025-08-06 Added version history and rework instructions for V0.1
2025-08-06 added supporting images
2025-08-06 moved rework instruction as per version
2025-08-06 Rename Project_OAK_MAIN_BRD_V0.1_Rework.md to README.md
2025-08-06 Updated V0.1 Rework link
2025-08-06 Updated Rework Instruction image link
2025-08-17 added mechanical integration images
2025-08-17 Added images
2025-08-30 Create README.md
    Added a readme inside LLD to have a better understanding of the design changes in each version
2025-08-31 Added Project OAK Integration V0.1 STEP file
2025-08-31 added project OAK v0.1 working explanation
2025-09-01 renamed final code version from V1.0 to V0.1
2025-09-22 Added V1.0 design files
2025-09-23 Added V1.0 pinmap data and update schematics
2025-09-24 imported net list into layout
2025-10-05 updated main board
    changed main board stack up from 6L to 4L, updated schematics with symbol & footprint change for push button and updated main board outline with latest mechanical changes.
2025-10-19 Update version history
2025-10-19 Updated placement
2025-10-22 updated layout
2025-10-24 layout update
2025-10-26 update layout
2025-10-28 removed thermal vias from MCU
2025-10-29 added Gerber files
2025-11-16 added V1.0 BOM, updated greber
2025-11-18 SCH update in progress with ACCL sensor change & haptic sensor addition
2025-11-19 layout update in progress
2025-11-23 OAK V1.0 main board layout update
2025-11-24 OAK V1.0 main board routing complete
2025-12-01 updated PCB and Gerber with final mechanical fitment
2025-12-09 Final files prior to DFM check
2025-12-14 updated PCB based on JLCPCB DFM comments and generated final files
2026-06-21 files moved around the folders

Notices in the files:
parts and their libraries:
Copyright 2016 Accelerated Designs. All rights reserved.
